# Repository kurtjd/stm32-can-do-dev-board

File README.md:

# STM32 CAN-Do! Development Board
|Layout|3D View|
|------|-------|
|||

A development board featuring:
- A STM32F103C8 microcontroller
- External high-speed crystal oscillator
- GPIO breakout, SWD and USB connectors
- CAN transceiver
- 5V LDO regulator
- 24V buck converter

This was primarily designed for testing CAN communication and voltage regulation before a
final design which will be used in the OSU DAM Robotics Club Mars Rover gripper.

This board is a bit of a step up in complexity from my previous boards, and due to
time constraints, wasn't able to do as much due dillgence and research as I'd have likes.

In future boards/revisions, I would like to revisit voltage regulators as newer chips
could be used and give more care to layout (which is not done as well as it could be here).
Also plan to learn more about designing 4-layer boards as the CAN and USB signal routing here
is not great at all and could use additional layers for signal integrity and ease of routing.

## Schematic
See `stm32-can-do-schematic.pdf` for full board schematic.

## Manufacturing
See the `KiCad/Manufacturing` folder. This contains the necessary
Gerber and BOM files for manufacturing by JLCPCB.

## License
This project is licensed under the MIT license and is completely free to use and modify.

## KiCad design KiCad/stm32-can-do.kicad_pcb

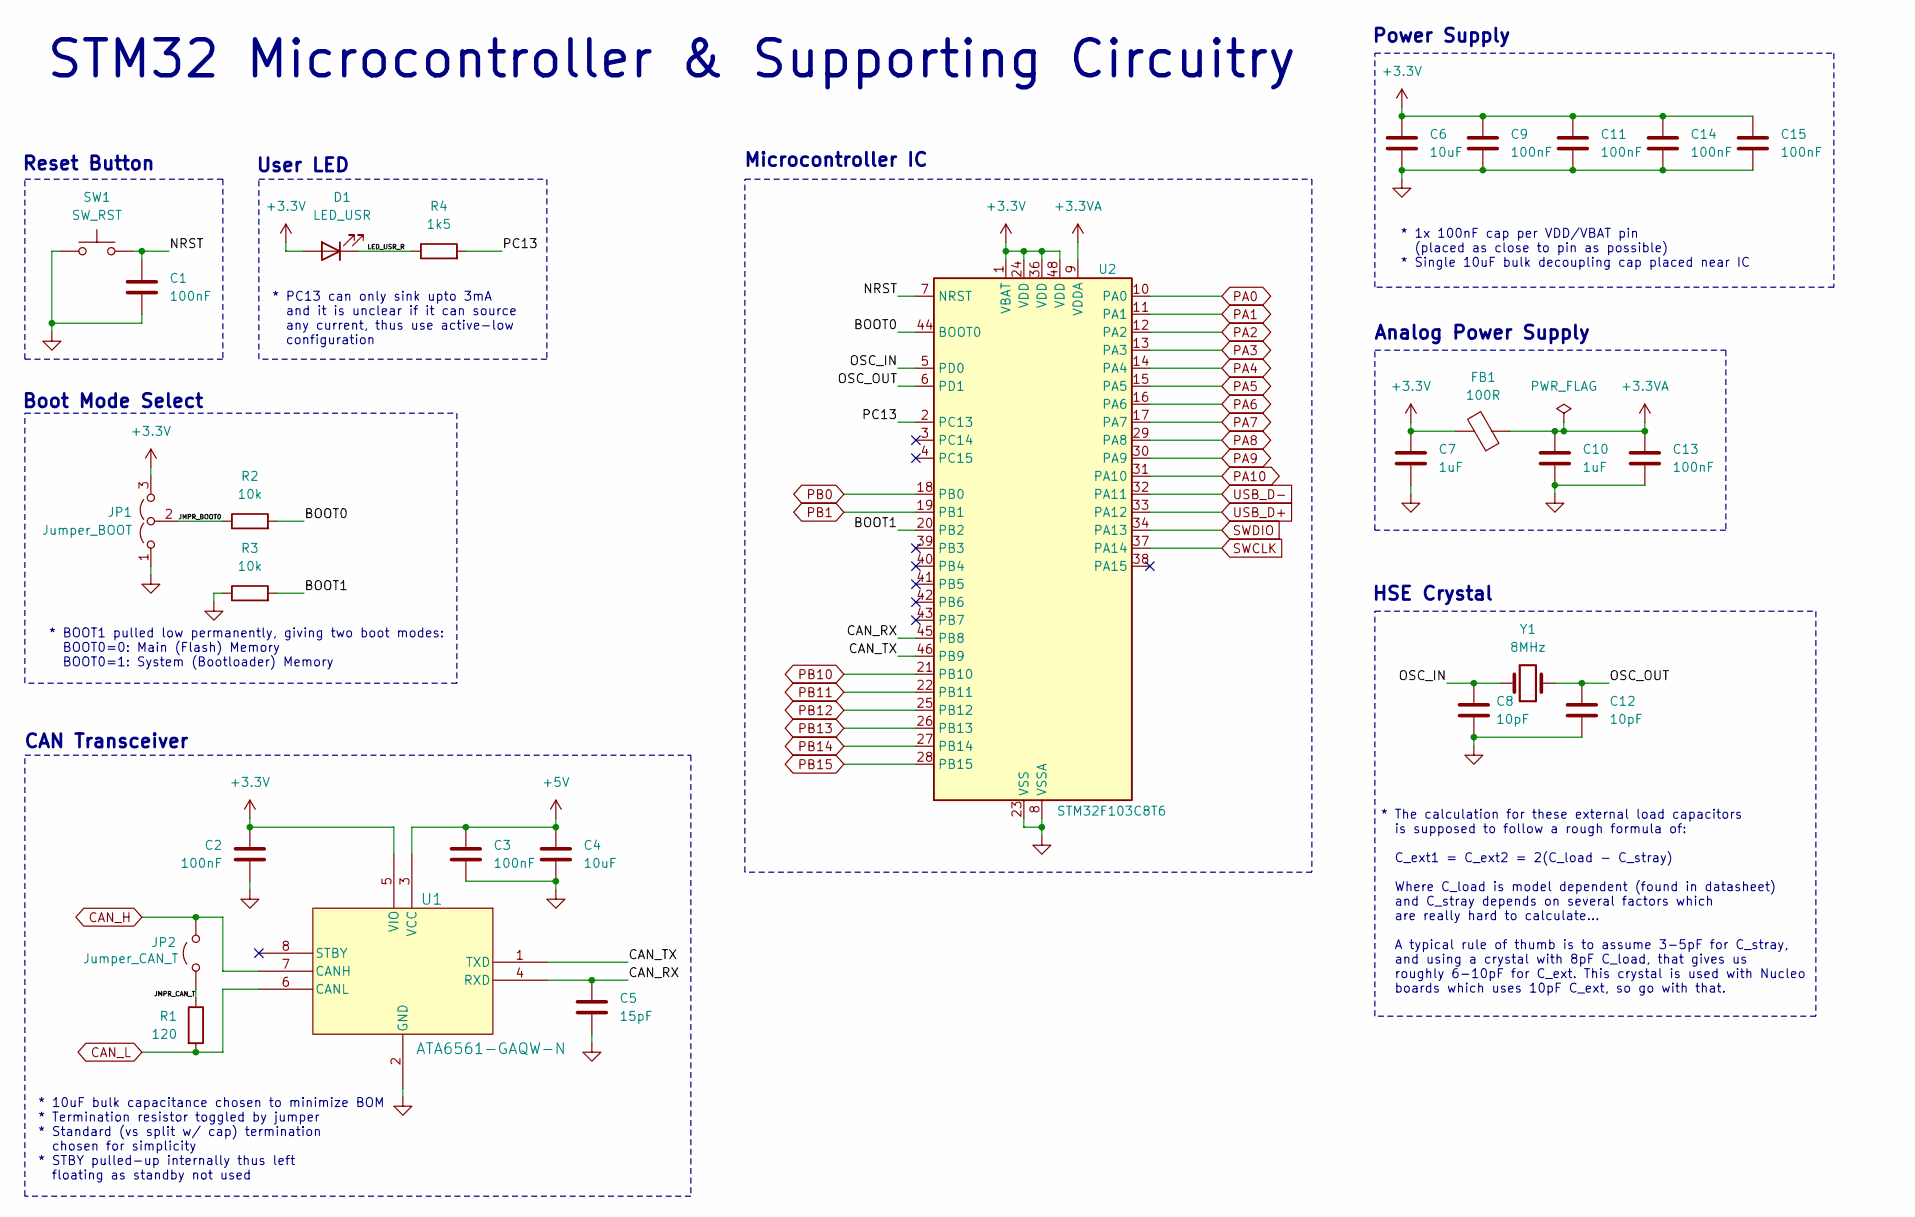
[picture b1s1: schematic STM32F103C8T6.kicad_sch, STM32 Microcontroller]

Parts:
C1, C2, C3, C9, C11, C13, C14, C15: 100nF; C_0402_1005Metric; LCSC C1525
C4, C6: 10uF; C_0603_1608Metric; LCSC C19702
C5: 15pF; C_0402_1005Metric; LCSC C1548
C7, C10: 1uF; C_0402_1005Metric; LCSC C52923
C8, C12: 10pF; C_0402_1005Metric; LCSC C32949
D1: LED_USR; LED_0603_1608Metric; LCSC C2286
FB1: 100R; L_0805_2012Metric; LCSC C1015
JP1: Jumper_BOOT; PinHeader_1x03_P2.54mm_Vertical
JP2: Jumper_CAN_T; PinHeader_1x02_P2.54mm_Vertical
R1: 120; R_0402_1005Metric; LCSC C25079
R2, R3: 10k; R_0402_1005Metric; LCSC C25744
R4: 1k5; R_0402_1005Metric; LCSC C25867
SW1: SW_RST; SW_PUSH_6mm
U1: ATA6561-GAQW-N; SOIC8_4P9X3P9MC_MCH; LCSC C616016
U2: STM32F103C8T6; LQFP-48_7x7mm_P0.5mm; LCSC C8734
Y1: 8MHz; XTAL_NX3225GD-8MHZ-STD-CRA-3_NDK; LCSC C889706

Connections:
+3.3V: C2.1, C6.1, C7.1, C9.1, C11.1, C14.1, C15.1, D1.2 (A), FB1.2, JP1.3 (B), U1.5 (VIO), U2.1 (VBAT), U2.24 (VDD), U2.36 (VDD), U2.48 (VDD); also elsewhere on the board
+3.3VA: C10.1, C13.1, FB1.1, U2.9 (VDDA)
+5V: C3.1, C4.1, U1.3 (VCC); also elsewhere on the board
/STM32F103C8T6/BOOT0: R2.2, U2.44 (BOOT0)
/STM32F103C8T6/BOOT1: R3.2, U2.20 (PB2)
/STM32F103C8T6/CAN_RX: C5.1, U1.4 (RXD), U2.45 (PB8)
/STM32F103C8T6/CAN_TX: U1.1 (TXD), U2.46 (PB9)
/STM32F103C8T6/JMPR_BOOT0: JP1.2 (C), R2.1
/STM32F103C8T6/JMPR_CAN_T: JP2.1 (A), R1.1
/STM32F103C8T6/LED_USR_R: D1.1 (K), R4.1
/STM32F103C8T6/NRST: C1.1, SW1.2, U2.7 (NRST)
/STM32F103C8T6/OSC_IN: C8.2, U2.5 (PD0), Y1.2
/STM32F103C8T6/OSC_OUT: C12.2, U2.6 (PD1), Y1.1
/STM32F103C8T6/PC13: R4.2, U2.2 (PC13)
CAN_H: JP2.2 (B), U1.7 (CANH); also elsewhere on the board
CAN_L: R1.2, U1.6 (CANL); also elsewhere on the board
GND: C1.2, C2.2, C3.2, C4.2, C5.2, C6.2, C7.2, C8.1, C9.2, C10.2, C11.2, C12.1, C13.2, C14.2, C15.2, JP1.1 (A), R3.1, SW1.1, U1.2 (GND), U2.8 (VSSA), U2.23 (VSS), U2.35 (VSS), U2.47 (VSS); also elsewhere on the board
PA0: U2.10 (PA0); also elsewhere on the board
PA1: U2.11 (PA1); also elsewhere on the board
PA2: U2.12 (PA2); also elsewhere on the board
PA3: U2.13 (PA3); also elsewhere on the board
PA4: U2.14 (PA4); also elsewhere on the board
PA5: U2.15 (PA5); also elsewhere on the board
PA6: U2.16 (PA6); also elsewhere on the board
PA7: U2.17 (PA7); also elsewhere on the board
PA8: U2.29 (PA8); also elsewhere on the board
PA9: U2.30 (PA9); also elsewhere on the board
PA10: U2.31 (PA10); also elsewhere on the board
PB0: U2.18 (PB0); also elsewhere on the board
PB1: U2.19 (PB1); also elsewhere on the board
PB10: U2.21 (PB10); also elsewhere on the board
PB11: U2.22 (PB11); also elsewhere on the board
PB12: U2.25 (PB12); also elsewhere on the board
PB13: U2.26 (PB13); also elsewhere on the board
PB14: U2.27 (PB14); also elsewhere on the board
PB15: U2.28 (PB15); also elsewhere on the board
SWCLK: U2.37 (PA14); also elsewhere on the board
SWDIO: U2.34 (PA13); also elsewhere on the board
USB_D+: U2.33 (PA12); also elsewhere on the board
USB_D-: U2.32 (PA11); also elsewhere on the board

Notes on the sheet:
* PC13 can only sink upto 3mA and it is unclear if it can source any current, thus use active-low configuration
Power Supply
Boot Mode Select
User LED
Microcontroller IC
Reset Button
* BOOT1 pulled low permanently, giving two boot modes: BOOT0=0: Main (Flash) Memory BOOT0=1: System (Bootloader) Memory
* The calculation for these external load capacitors is supposed to follow a rough formula of: C_ext1 = C_ext2 = 2(C_load - C_stray) Where C_load is model dependent (found in datasheet) and C_stray depends on several factors which are really hard to calculate... A typical rule of thumb is to assume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
CAN Transceiver
HSE Crystal
* 1x 100nF cap per VDD/VBAT pin (placed as close to pin as possible) * Single 10uF bulk decoupling cap placed near IC
STM32 Microcontroller & Supporting Circuitry
Analog Power Supply
* 10uF bulk capacitance chosen to minimize BOM * Termination resistor toggled by jumper * Standard (vs split w/ cap) termination chosen for simplicity * STBY pulled-up internally thus left floating as standby not used

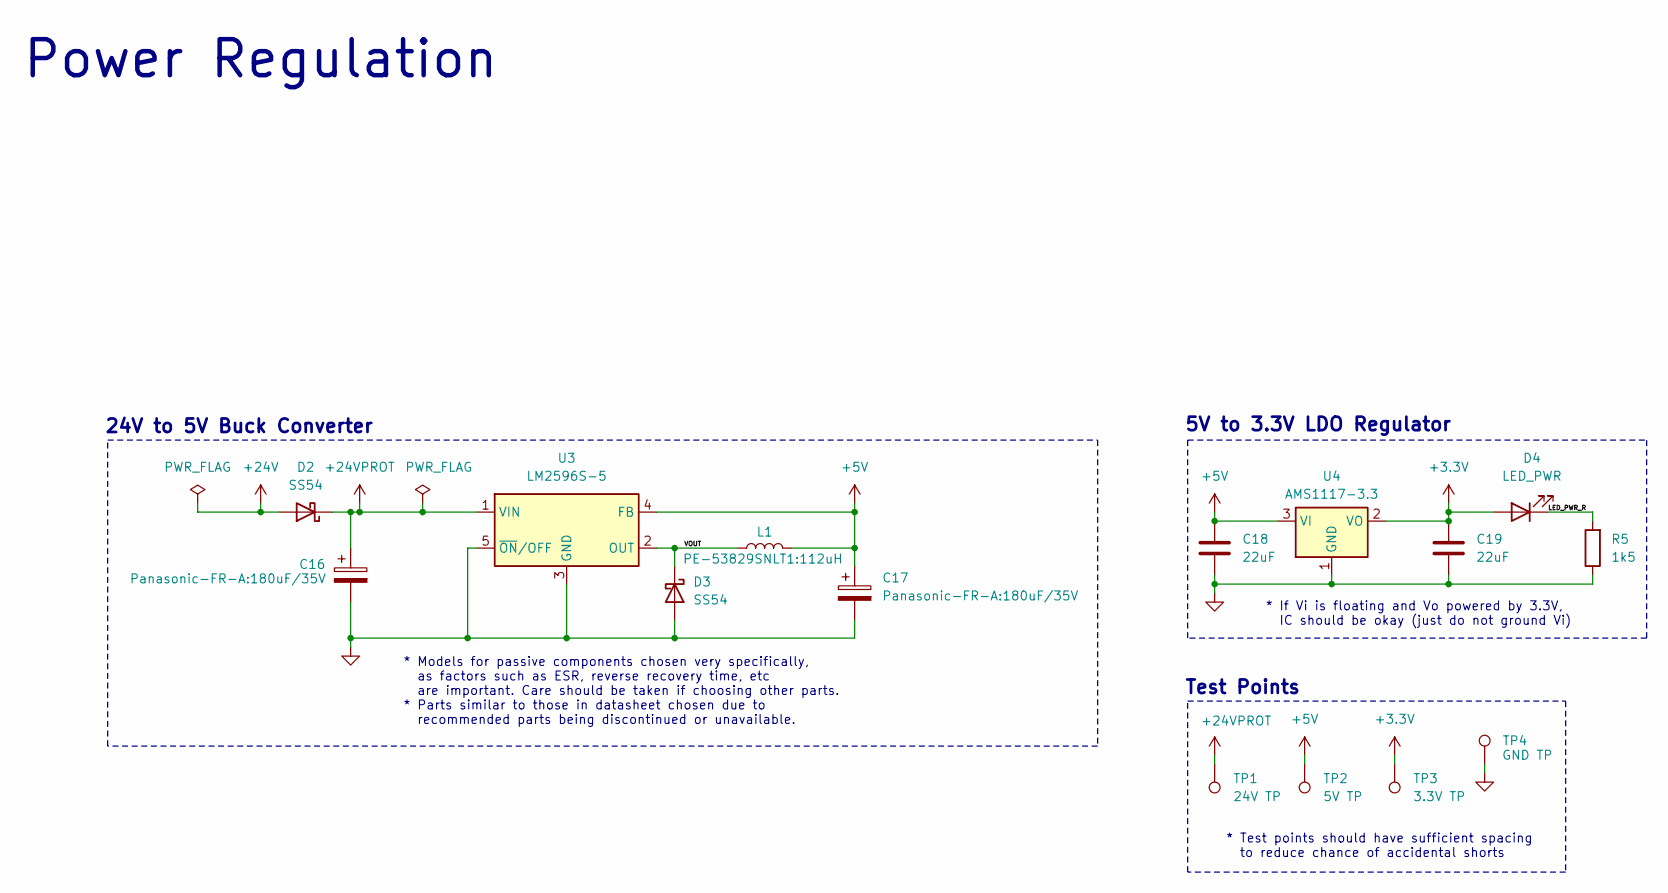
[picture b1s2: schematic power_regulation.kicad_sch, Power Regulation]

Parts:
C16, C17: Panasonic-FR-A:180uF/35V; CP_Radial_D8.0mm_P5.00mm
C18, C19: 22uF; C_0805_2012Metric; LCSC C45783
D2, D3: SS54; D_SMA; LCSC C22452
D4: LED_PWR; LED_0603_1608Metric; LCSC C2286
L1: PE-53829SNLT1:112uH; IND_829SNLT_PUL; LCSC C2453068
R5: 1k5; R_0402_1005Metric; LCSC C25867
TP1: 24V TP; PinHeader_1x01_P2.54mm_Vertical
TP2: 5V TP; PinHeader_1x01_P2.54mm_Vertical
TP3: 3.3V TP; PinHeader_1x01_P2.54mm_Vertical
TP4: GND TP; PinHeader_1x01_P2.54mm_Vertical
U3: LM2596S-5; TO-263-5_TabPin3; LCSC C347421
U4: AMS1117-3.3; SOT-223-3_TabPin2; LCSC C6186

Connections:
+3.3V: C19.1, D4.2 (A), TP3.1, U4.2 (VO); also elsewhere on the board
+5V: C17.1, C18.1, L1.2, TP2.1, U3.4 (FB), U4.3 (VI); also elsewhere on the board
+24V: D2.2 (A); also elsewhere on the board
+24VPROT: C16.1, D2.1 (K), TP1.1, U3.1 (VIN)
/Power Regulation/LED_PWR_R: D4.1 (K), R5.2
/Power Regulation/VOUT: D3.1 (K), L1.1, U3.2 (OUT)
GND: C16.2, C17.2, C18.2, C19.2, D3.2 (A), R5.1, TP4.1, U3.3 (GND), U3.5 (~ON/OFF), U4.1 (GND); also elsewhere on the board

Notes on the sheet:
24V to 5V Buck Converter
5V to 3.3V LDO Regulator
* If Vi is floating and Vo powered by 3.3V, IC should be okay (just do not ground Vi)
Test Points
* Models for passive components chosen very specifically, as factors such as ESR, reverse recovery time, etc are important. Care should be taken if choosing other parts. * Parts similar to those in datasheet chosen due to recommended parts being discontinued or unavailable.
* Test points should have sufficient spacing to reduce chance of accidental shorts
Power Regulation

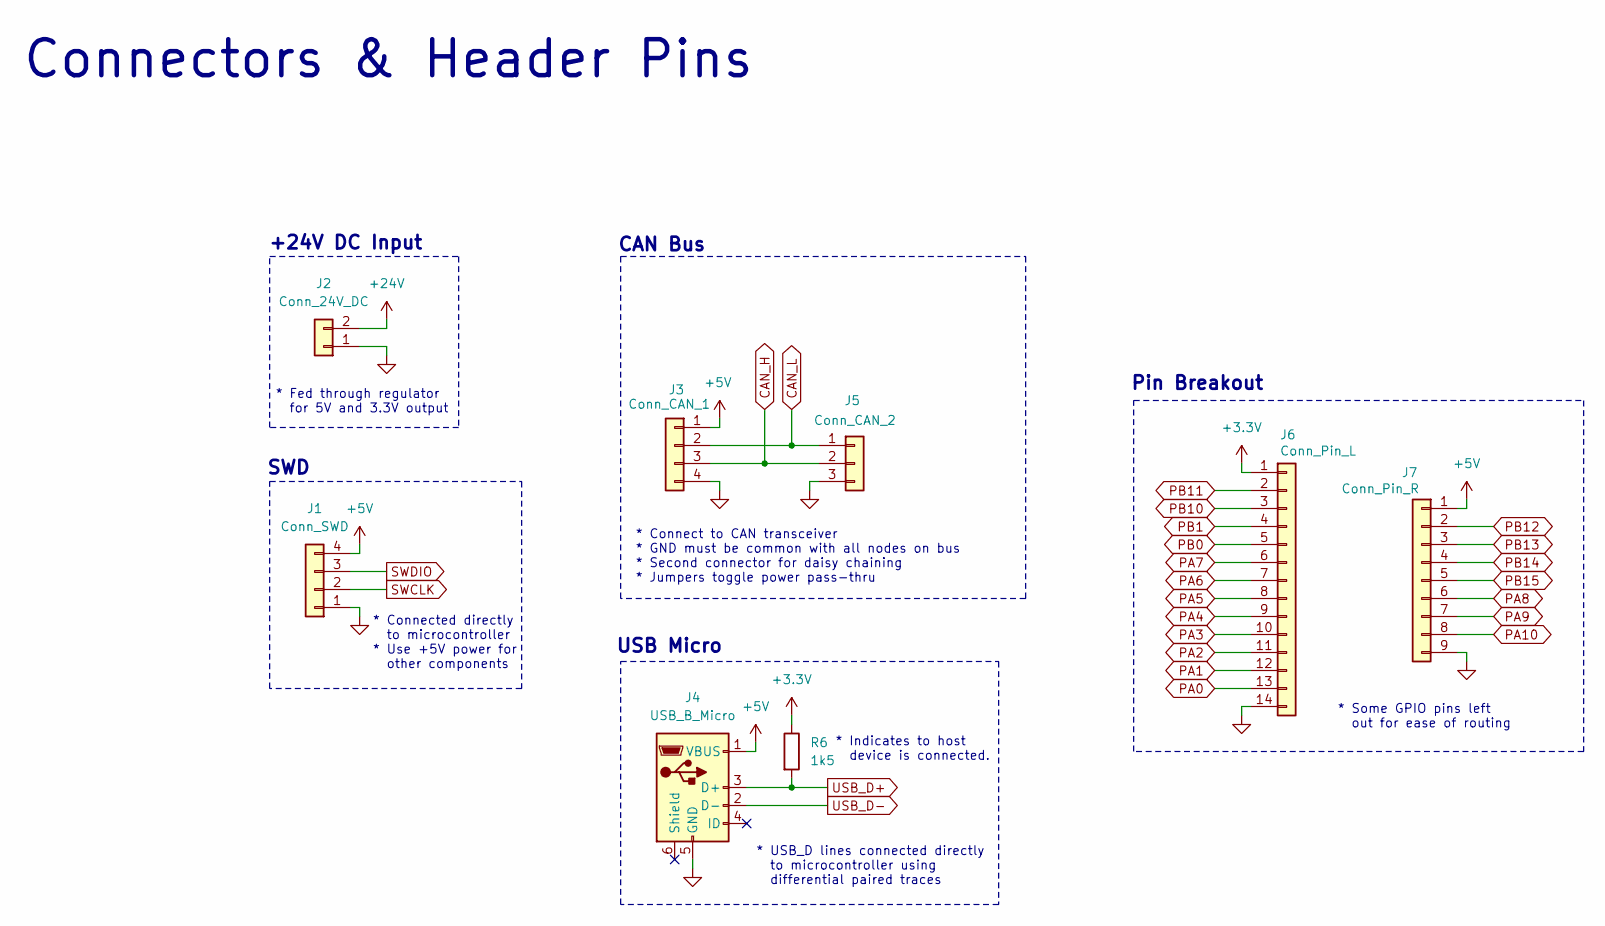
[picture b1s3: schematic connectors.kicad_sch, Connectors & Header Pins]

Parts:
J1: Conn_SWD; PinHeader_1x04_P2.54mm_Vertical
J2: Conn_24V_DC; PinHeader_1x02_P2.54mm_Vertical
J3: Conn_CAN_1; PinHeader_1x04_P2.54mm_Vertical
J4: USB_B_Micro; USB_Micro-B_Amphenol_10118194-0001LF_Horizontal; LCSC C132563
J5: Conn_CAN_2; PinHeader_1x03_P2.54mm_Vertical
J6: Conn_Pin_L; PinSocket_1x14_P2.54mm_Vertical
J7: Conn_Pin_R; PinSocket_1x09_P2.54mm_Vertical
R6: 1k5; R_0402_1005Metric; LCSC C25867

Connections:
+3.3V: J6.1, R6.1; also elsewhere on the board
+5V: J1.4, J3.1, J4.1 (VBUS), J7.1; also elsewhere on the board
+24V: J2.2; also elsewhere on the board
CAN_H: J3.3, J5.2; also elsewhere on the board
CAN_L: J3.2, J5.1; also elsewhere on the board
GND: J1.1, J2.1, J3.4, J4.5 (GND), J5.3, J6.14, J7.9; also elsewhere on the board
PA0: J6.13; also elsewhere on the board
PA1: J6.12; also elsewhere on the board
PA2: J6.11; also elsewhere on the board
PA3: J6.10; also elsewhere on the board
PA4: J6.9; also elsewhere on the board
PA5: J6.8; also elsewhere on the board
PA6: J6.7; also elsewhere on the board
PA7: J6.6; also elsewhere on the board
PA8: J7.6; also elsewhere on the board
PA9: J7.7; also elsewhere on the board
PA10: J7.8; also elsewhere on the board
PB0: J6.5; also elsewhere on the board
PB1: J6.4; also elsewhere on the board
PB10: J6.3; also elsewhere on the board
PB11: J6.2; also elsewhere on the board
PB12: J7.2; also elsewhere on the board
PB13: J7.3; also elsewhere on the board
PB14: J7.4; also elsewhere on the board
PB15: J7.5; also elsewhere on the board
SWCLK: J1.2; also elsewhere on the board
SWDIO: J1.3; also elsewhere on the board
USB_D+: J4.3 (D+), R6.2; also elsewhere on the board
USB_D-: J4.2 (D-); also elsewhere on the board

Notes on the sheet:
* Fed through regulator for 5V and 3.3V output
Pin Breakout
SWD
* Some GPIO pins left out for ease of routing
* Connect to CAN transceiver * GND must be common with all nodes on bus * Second connector for daisy chaining * Jumpers toggle power pass-thru
+24V DC Input
Connectors & Header Pins
* Indicates to host device is connected.
* Connected directly to microcontroller * Use +5V power for other components
* USB_D lines connected directly to microcontroller using differential paired traces
USB Micro
CAN Bus

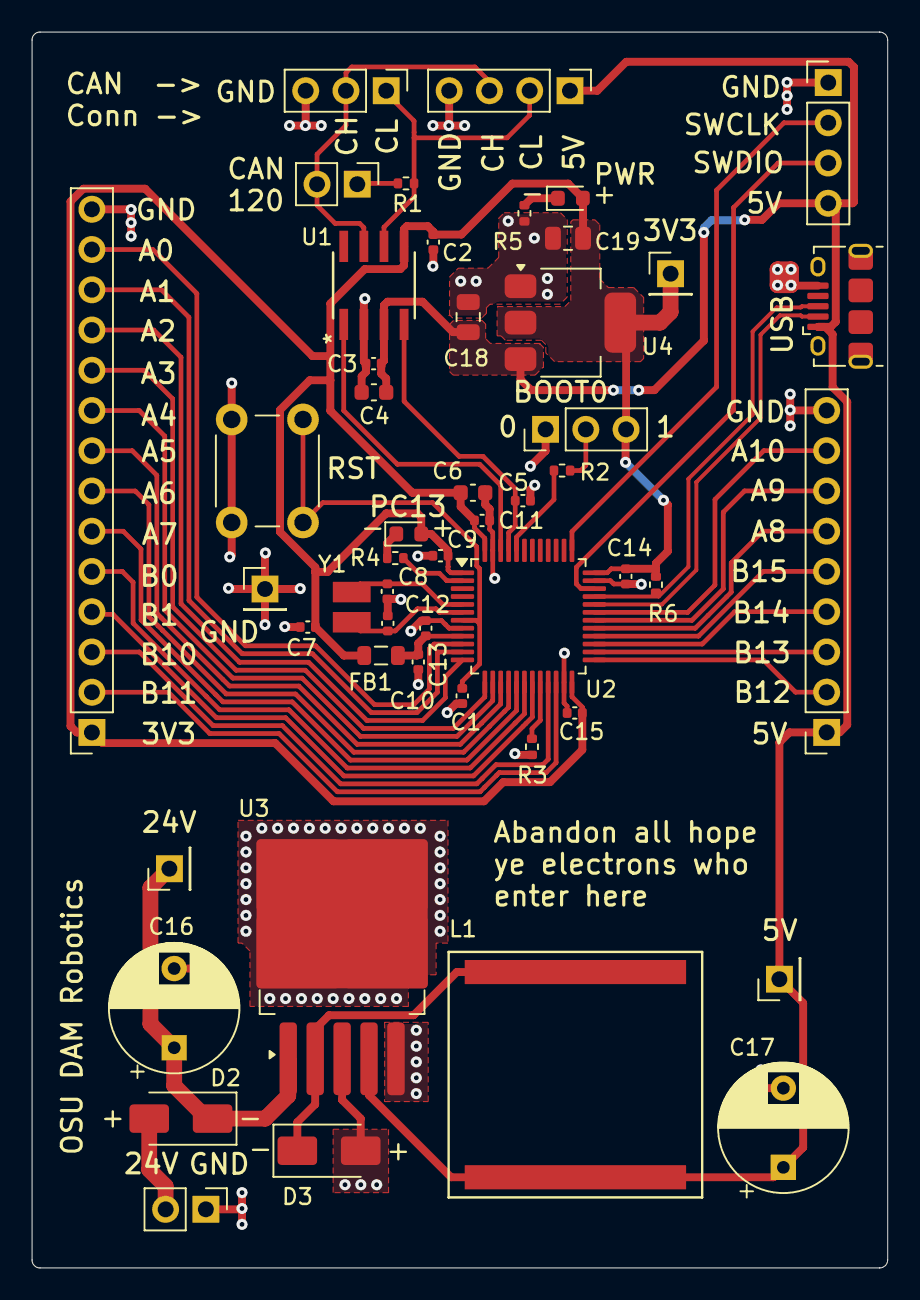
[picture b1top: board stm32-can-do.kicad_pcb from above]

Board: 2 copper layers, 54.0 x 78.0 mm, 50 parts (0 on the bottom side), 44 nets.

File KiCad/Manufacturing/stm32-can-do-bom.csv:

"Reference","Value","Footprint","Qty","LCSC"
"C1,C2,C3,C9,C11,C13,C14,C15","100nF","Capacitor_SMD:C_0402_1005Metric","8","C1525"
"C4,C6","10uF","Capacitor_SMD:C_0603_1608Metric","2","C19702"
"C5","15pF","Capacitor_SMD:C_0402_1005Metric","1","C1548"
"C7,C10","1uF","Capacitor_SMD:C_0402_1005Metric","2","C52923"
"C8,C12","10pF","Capacitor_SMD:C_0402_1005Metric","2","C32949"
"C18,C19","22uF","Capacitor_SMD:C_0805_2012Metric","2","C45783"
"D1","LED_USR","LED_SMD:LED_0603_1608Metric","1","C2286"
"D2,D3","SS54","Diode_SMD:D_SMA","2","C22452"
"D4","LED_PWR","LED_SMD:LED_0603_1608Metric","1","C2286"
"FB1","100R","Inductor_SMD:L_0805_2012Metric","1","C1015"
"J4","USB_B_Micro","Connector_USB:USB_Micro-B_Amphenol_10118194-0001LF_Horizontal","1","C132563"
"L1","PE-53829SNLT1:112uH","PE53829SNLT:IND_829SNLT_PUL","1","C2453068"
"R1","120","Resistor_SMD:R_0402_1005Metric","1","C25079"
"R2,R3","10k","Resistor_SMD:R_0402_1005Metric","2","C25744"
"R4,R5,R6","1k5","Resistor_SMD:R_0402_1005Metric","3","C25867"
"U1","ATA6561-GAQW-N","ATA6561:SOIC8_4P9X3P9MC_MCH","1","C616016"
"U2","STM32F103C8T6","Package_QFP:LQFP-48_7x7mm_P0.5mm","1","C8734"
"U3","LM2596S-5","Package_TO_SOT_SMD:TO-263-5_TabPin3","1","C347421"
"U4","AMS1117-3.3","Package_TO_SOT_SMD:SOT-223-3_TabPin2","1","C6186"
"Y1","8MHz","NX3225GD:XTAL_NX3225GD-8MHZ-STD-CRA-3_NDK","1","C889706"
